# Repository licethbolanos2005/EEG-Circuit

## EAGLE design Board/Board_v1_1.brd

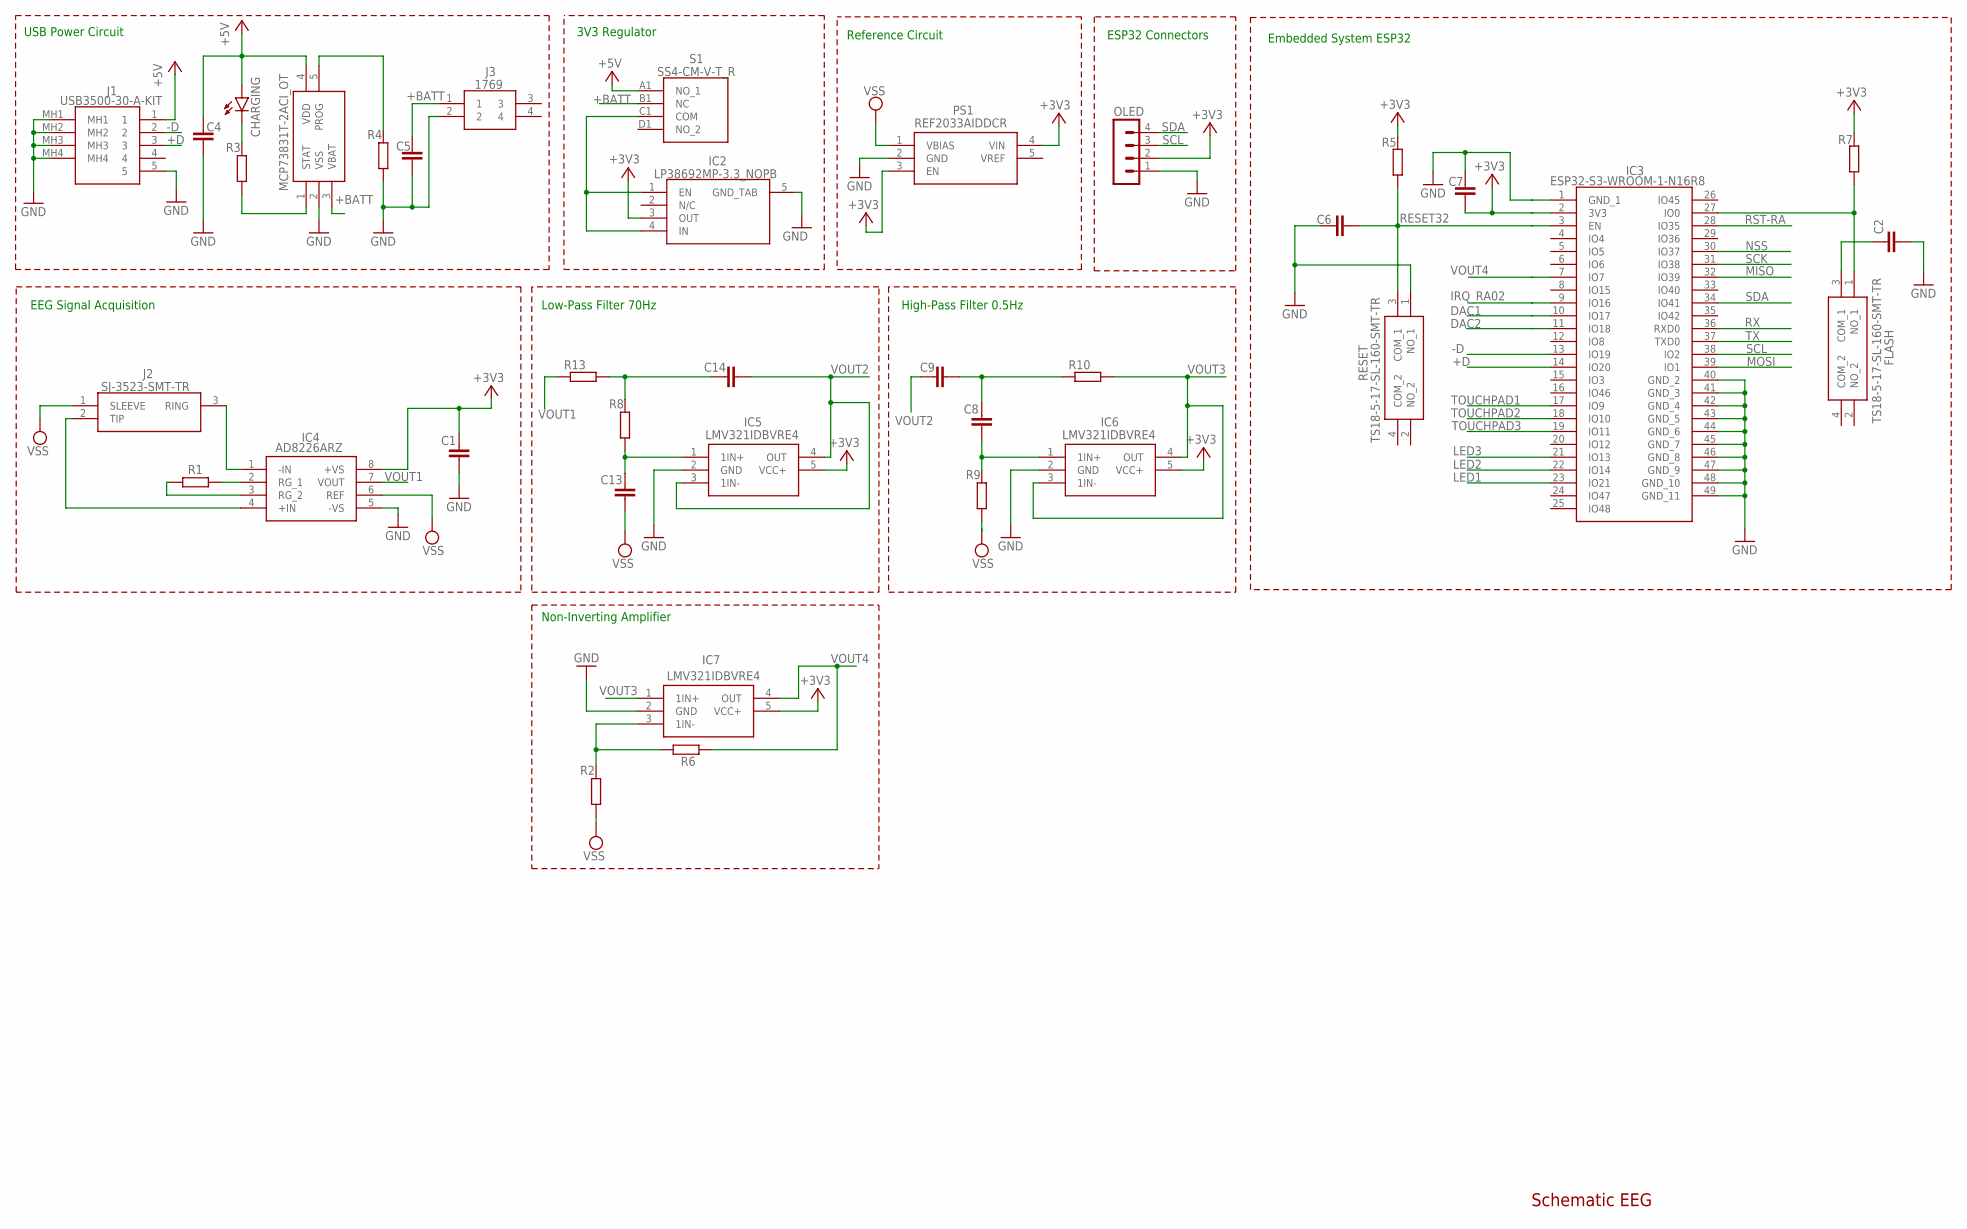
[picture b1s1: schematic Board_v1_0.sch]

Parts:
C1, C2, C4, C5, C6, C7, C8, C9, C13, C14: C-EUC0805; C0805
CHARGING: LEDCHIP-LED0805; CHIP-LED0805
FLASH: TS18-5-17-SL-160-SMT-TR; TS18517SL160SMTTR
IC1: MCP73831T-2ACI_OT; SOT95P270X145-5N
IC2: LP38692MP-3.3_NOPB; SOT150P700X180-5N
IC3: ESP32-S3-WROOM-1-N16R8; ESP32S3WROOM1N16R8
IC4: AD8226ARZ; SOIC127P600X175-8N
IC5, IC6, IC7: LMV321IDBVRE4; SOT95P280X145-5N
J1: USB3500-30-A-KIT; USB350030AKIT
J2: SJ-3523-SMT-TR; SJ3523SMTTR
J3: 1769
OLED: MA04-1
PS1: REF2033AIDDCR; SOT95P280X110-5N
R1, R2, R4, R5, R6, R7, R8, R9, R10, R13: R-EU_R0805; R0805
R3: 220; R0805
RESET: TS18-5-17-SL-160-SMT-TR; TS18517SL160SMTTR
S1: SS4-CM-V-T_R; SS4CMVTR

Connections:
+3V3: C1.1, C7.2, IC2.3 (OUT), IC3.2 (3V3), IC4.8 (+VS), IC5.5 (VCC+), IC6.5 (VCC+), IC7.5 (VCC+), OLED.2, PS1.3 (EN), PS1.4 (VIN), R5.2, R7.2
+BATT: C5.2, IC1.3 (VBAT), J3.1, S1.B1 (NC)
+D: IC3.14 (IO20), J1.3
-D: IC3.13 (IO19), J1.2
DAC1: IC3.10 (IO17)
DAC2: IC3.11 (IO18)
IRQ_RA02: IC3.9 (IO16)
LED1: IC3.23 (IO21)
LED2: IC3.22 (IO14)
LED3: IC3.21 (IO13)
MISO: IC3.32 (IO39)
MOSI: IC3.39 (IO1)
unnamed: IC4.2 (RG_1), R1.2
unnamed: IC4.3 (RG_2), R1.1
unnamed: IC4.1 (-IN), J2.3 (RING)
unnamed: IC4.4 (+IN), J2.2 (TIP)
unnamed: C8.2, IC6.1 (1IN+), R9.2
unnamed: IC1.1 (STAT), R3.1
unnamed: IC1.5 (PROG), R4.2
unnamed 19: CHARGING.C, R3.2; also elsewhere on the board
unnamed: C8.1, C9.2, R10.1
unnamed: C13.1, IC5.1 (1IN+), R8.1
unnamed: IC2.1 (EN), IC2.4 (IN), S1.C1 (COM)
unnamed: IC7.3 (1IN-), R2.2, R6.2
unnamed: C14.1, R8.2, R13.2
NSS: IC3.30 (IO37)
RESET32: C6.2, IC3.3 (EN), R5.1, RESET.3 (COM_1)
RST-RA: IC3.28 (IO35)
RX: IC3.36 (RXD0)
SCK: IC3.31 (IO38)
SCL: IC3.38 (IO2), OLED.3
SDA: IC3.34 (IO41), OLED.4
TOUCHPAD1: IC3.17 (IO9)
TOUCHPAD2: IC3.18 (IO10)
TOUCHPAD3: IC3.19 (IO11)
TX: IC3.37 (TXD0)
VOUT1: IC4.7 (VOUT), R13.1
VOUT2: C9.1, C14.2, IC5.3 (1IN-), IC5.4 (OUT)
VOUT3: IC6.3 (1IN-), IC6.4 (OUT), IC7.1 (1IN+), R10.2
VOUT4: IC3.7 (IO7), IC7.4 (OUT), R6.1
VSS: C13.2, IC4.6 (REF), J2.1 (SLEEVE), PS1.1 (VBIAS), R2.1, R9.1

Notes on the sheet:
Schematic EEG
USB Power Circuit
3V3 Regulator
Reference Circuit
Embedded System ESP32
ESP32 Connectors
Low-Pass Filter 70Hz
High-Pass Filter 0.5Hz
EEG Signal Acquisition
Non-Inverting Amplifier

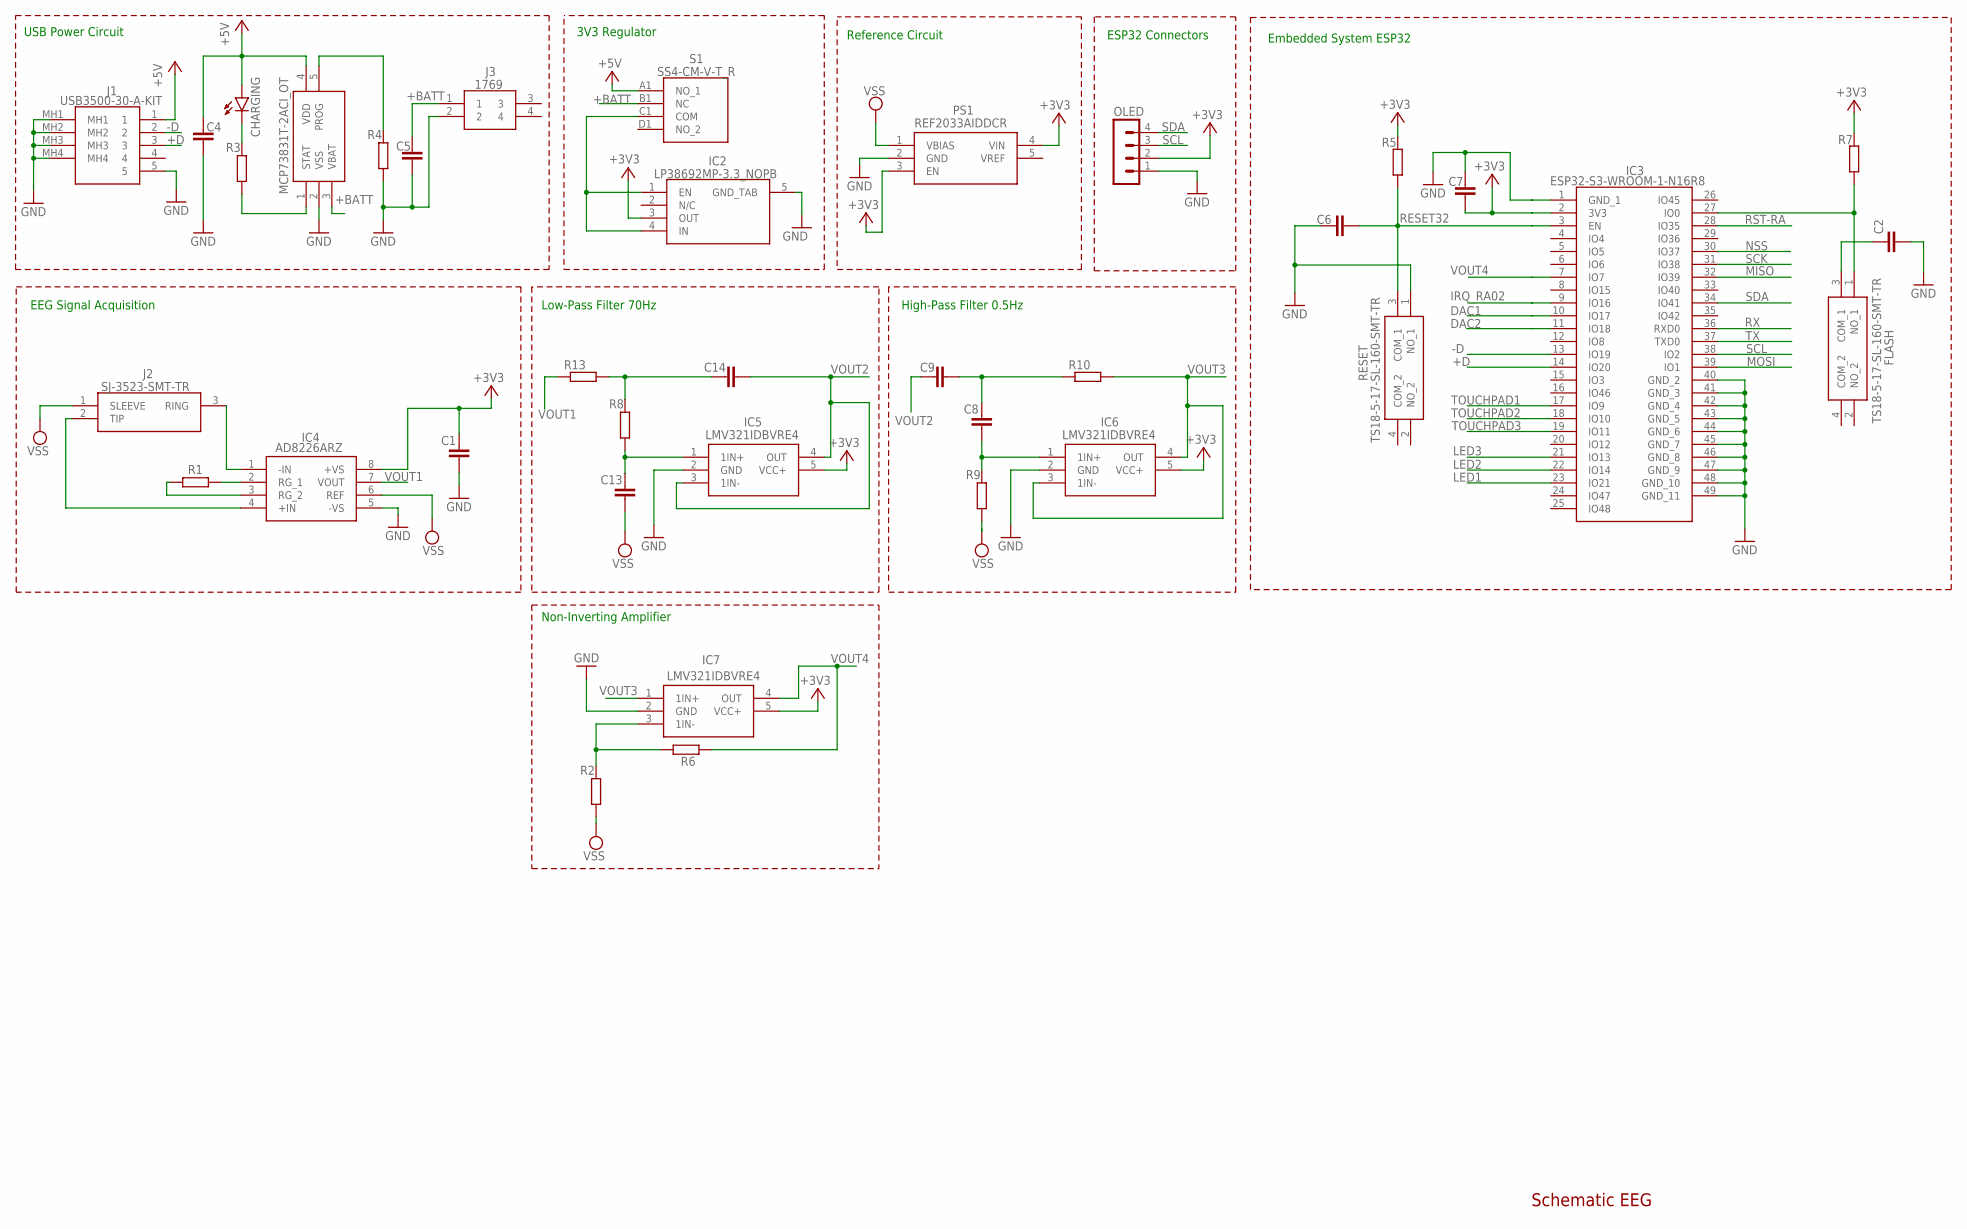
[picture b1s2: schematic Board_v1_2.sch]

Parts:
C1, C2, C4, C5, C6, C7, C8, C9, C13, C14: C-EUC0805; C0805
CHARGING: LEDCHIP-LED0805; CHIP-LED0805
FLASH: TS18-5-17-SL-160-SMT-TR; TS18517SL160SMTTR
IC1: MCP73831T-2ACI_OT; SOT95P270X145-5N
IC2: LP38692MP-3.3_NOPB; SOT150P700X180-5N
IC3: ESP32-S3-WROOM-1-N16R8; ESP32S3WROOM1N16R8
IC4: AD8226ARZ; SOIC127P600X175-8N
IC5, IC6, IC7: LMV321IDBVRE4; SOT95P280X145-5N
J1: USB3500-30-A-KIT; USB350030AKIT
J2: SJ-3523-SMT-TR; SJ3523SMTTR
J3: 1769
OLED: MA04-1
PS1: REF2033AIDDCR; SOT95P280X110-5N
R1, R2, R4, R5, R6, R7, R8, R9, R10, R13: R-EU_R0805; R0805
R3: 220; R0805
RESET: TS18-5-17-SL-160-SMT-TR; TS18517SL160SMTTR
S1: SS4-CM-V-T_R; SS4CMVTR

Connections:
+3V3: C1.1, C7.2, IC2.3 (OUT), IC3.2 (3V3), IC4.8 (+VS), IC5.5 (VCC+), IC6.5 (VCC+), IC7.5 (VCC+), OLED.2, PS1.3 (EN), PS1.4 (VIN), R5.2, R7.2
+BATT: C5.2, IC1.3 (VBAT), J3.1, S1.B1 (NC)
+D: IC3.14 (IO20), J1.3
-D: IC3.13 (IO19), J1.2
DAC1: IC3.10 (IO17)
DAC2: IC3.11 (IO18)
IRQ_RA02: IC3.9 (IO16)
LED1: IC3.23 (IO21)
LED2: IC3.22 (IO14)
LED3: IC3.21 (IO13)
MISO: IC3.32 (IO39)
MOSI: IC3.39 (IO1)
unnamed: IC4.2 (RG_1), R1.2
unnamed: IC4.3 (RG_2), R1.1
unnamed: IC4.1 (-IN), J2.3 (RING)
unnamed: IC4.4 (+IN), J2.2 (TIP)
unnamed: C8.2, IC6.1 (1IN+), R9.2
unnamed: IC1.1 (STAT), R3.1
unnamed: IC1.5 (PROG), R4.2
unnamed 19: CHARGING.C, R3.2; also elsewhere on the board
unnamed: C8.1, C9.2, R10.1
unnamed: C13.1, IC5.1 (1IN+), R8.1
unnamed: IC2.1 (EN), IC2.4 (IN), S1.C1 (COM)
unnamed: IC7.3 (1IN-), R2.2, R6.2
unnamed: C14.1, R8.2, R13.2
NSS: IC3.30 (IO37)
RESET32: C6.2, IC3.3 (EN), R5.1, RESET.3 (COM_1)
RST-RA: IC3.28 (IO35)
RX: IC3.36 (RXD0)
SCK: IC3.31 (IO38)
SCL: IC3.38 (IO2), OLED.3
SDA: IC3.34 (IO41), OLED.4
TOUCHPAD1: IC3.17 (IO9)
TOUCHPAD2: IC3.18 (IO10)
TOUCHPAD3: IC3.19 (IO11)
TX: IC3.37 (TXD0)
VOUT1: IC4.7 (VOUT), R13.1
VOUT2: C9.1, C14.2, IC5.3 (1IN-), IC5.4 (OUT)
VOUT3: IC6.3 (1IN-), IC6.4 (OUT), IC7.1 (1IN+), R10.2
VOUT4: IC3.7 (IO7), IC7.4 (OUT), R6.1
VSS: C13.2, IC4.6 (REF), J2.1 (SLEEVE), PS1.1 (VBIAS), R2.1, R9.1

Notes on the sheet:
Schematic EEG
USB Power Circuit
3V3 Regulator
Reference Circuit
Embedded System ESP32
ESP32 Connectors
Low-Pass Filter 70Hz
High-Pass Filter 0.5Hz
EEG Signal Acquisition
Non-Inverting Amplifier

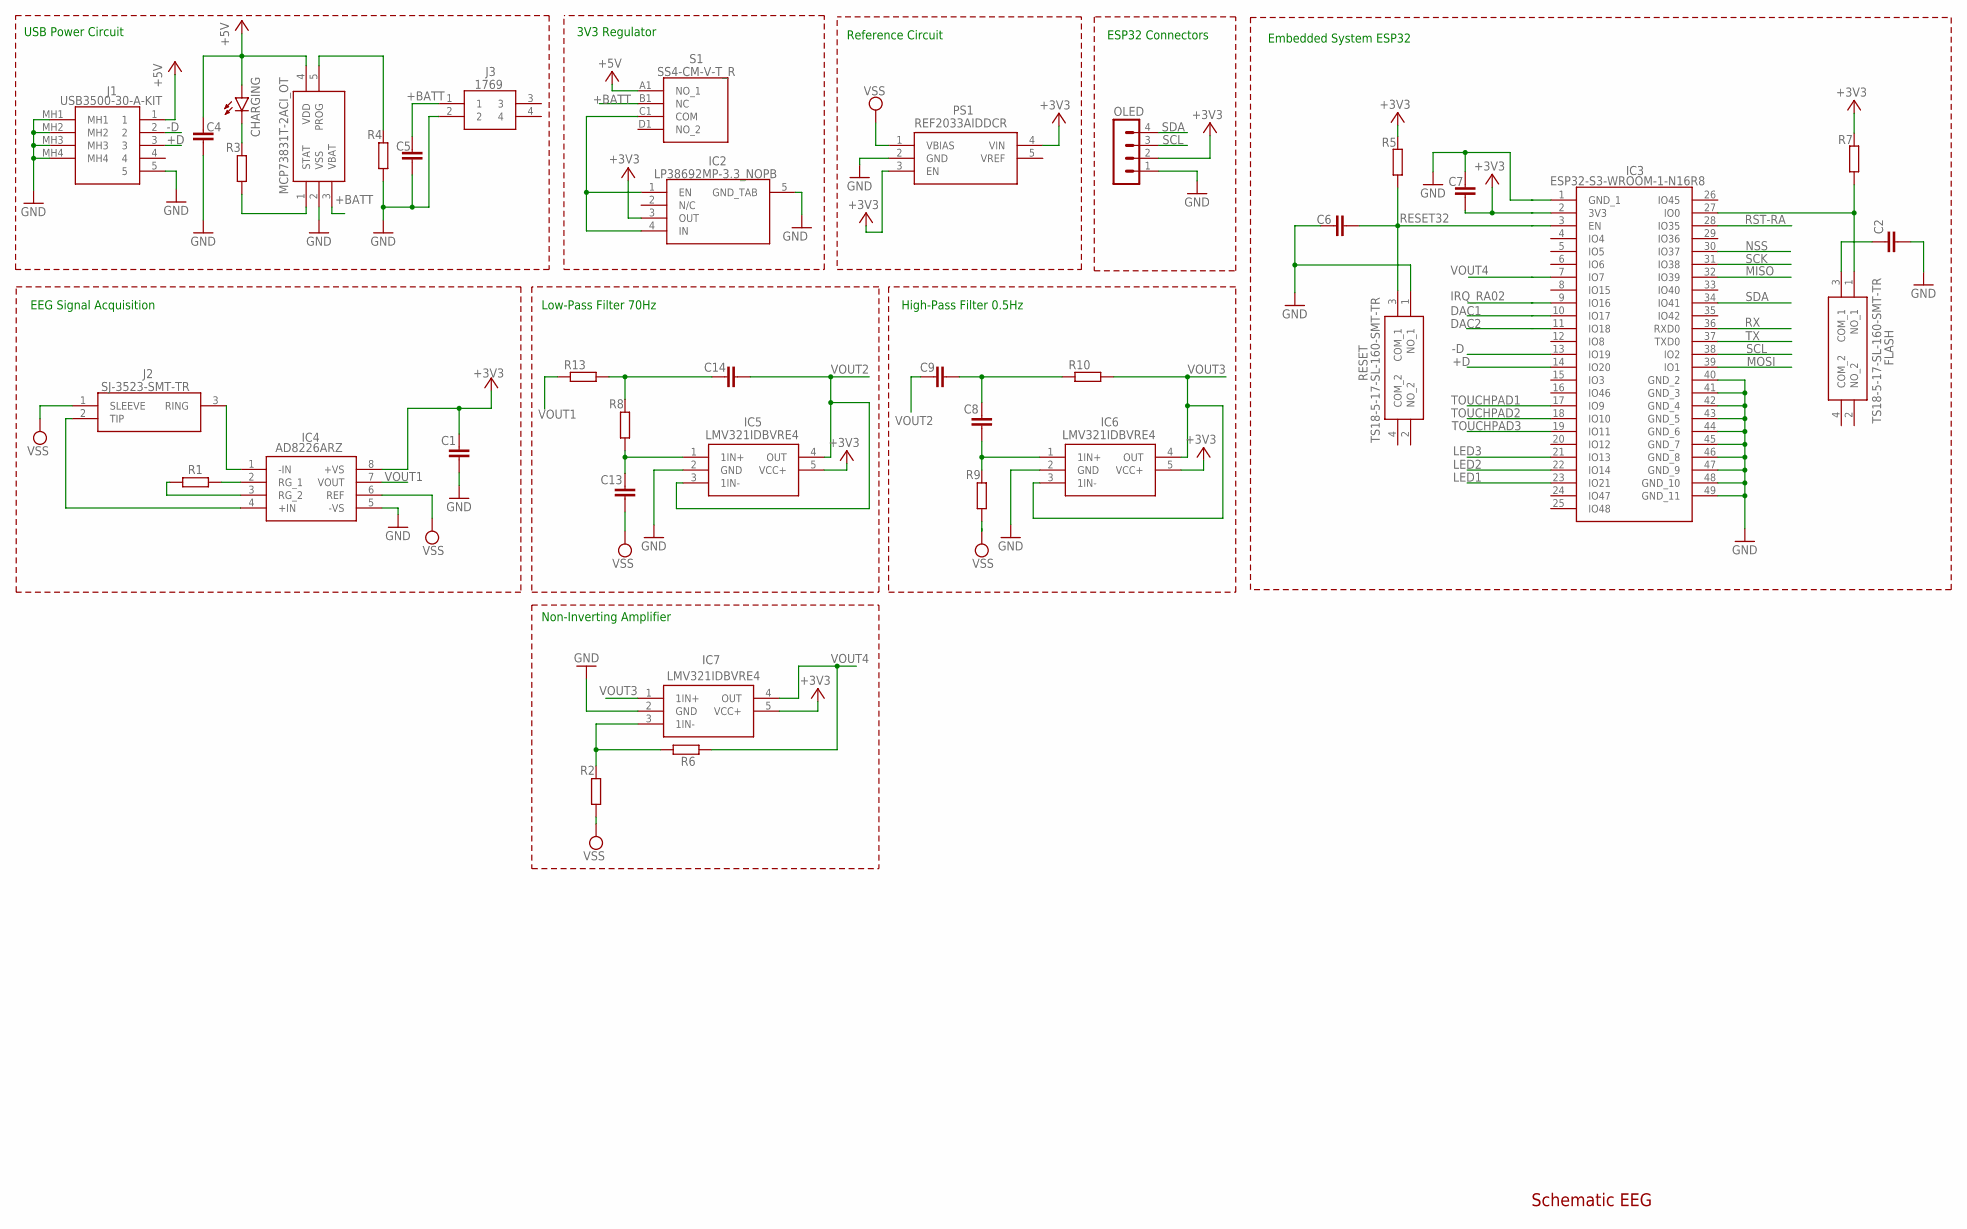
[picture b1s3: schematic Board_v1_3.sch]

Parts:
C1, C2, C4, C5, C6, C7, C8, C9, C13, C14: C-EUC0805; C0805
CHARGING: LEDCHIP-LED0805; CHIP-LED0805
FLASH: TS18-5-17-SL-160-SMT-TR; TS18517SL160SMTTR
IC1: MCP73831T-2ACI_OT; SOT95P270X145-5N
IC2: LP38692MP-3.3_NOPB; SOT150P700X180-5N
IC3: ESP32-S3-WROOM-1-N16R8; ESP32S3WROOM1N16R8
IC4: AD8226ARZ; SOIC127P600X175-8N
IC5, IC6, IC7: LMV321IDBVRE4; SOT95P280X145-5N
J1: USB3500-30-A-KIT; USB350030AKIT
J2: SJ-3523-SMT-TR; SJ3523SMTTR
J3: 1769
OLED: MA04-1
PS1: REF2033AIDDCR; SOT95P280X110-5N
R1, R2, R4, R5, R6, R7, R8, R9, R10, R13: R-EU_R0805; R0805
R3: 220; R0805
RESET: TS18-5-17-SL-160-SMT-TR; TS18517SL160SMTTR
S1: SS4-CM-V-T_R; SS4CMVTR

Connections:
+3V3: C1.1, C7.2, IC2.3 (OUT), IC3.2 (3V3), IC4.8 (+VS), IC5.5 (VCC+), IC6.5 (VCC+), IC7.5 (VCC+), OLED.2, PS1.3 (EN), PS1.4 (VIN), R5.2, R7.2
+BATT: C5.2, IC1.3 (VBAT), J3.1, S1.B1 (NC)
+D: IC3.14 (IO20), J1.3
-D: IC3.13 (IO19), J1.2
DAC1: IC3.10 (IO17)
DAC2: IC3.11 (IO18)
IRQ_RA02: IC3.9 (IO16)
LED1: IC3.23 (IO21)
LED2: IC3.22 (IO14)
LED3: IC3.21 (IO13)
MISO: IC3.32 (IO39)
MOSI: IC3.39 (IO1)
unnamed: IC4.2 (RG_1), R1.2
unnamed: IC4.3 (RG_2), R1.1
unnamed: IC4.1 (-IN), J2.3 (RING)
unnamed: IC4.4 (+IN), J2.2 (TIP)
unnamed: C8.2, IC6.1 (1IN+), R9.2
unnamed: IC1.1 (STAT), R3.1
unnamed: IC1.5 (PROG), R4.2
unnamed 19: CHARGING.C, R3.2; also elsewhere on the board
unnamed: C8.1, C9.2, R10.1
unnamed: C13.1, IC5.1 (1IN+), R8.1
unnamed: IC2.1 (EN), IC2.4 (IN), S1.C1 (COM)
unnamed: IC7.3 (1IN-), R2.2, R6.2
unnamed: C14.1, R8.2, R13.2
NSS: IC3.30 (IO37)
RESET32: C6.2, IC3.3 (EN), R5.1, RESET.3 (COM_1)
RST-RA: IC3.28 (IO35)
RX: IC3.36 (RXD0)
SCK: IC3.31 (IO38)
SCL: IC3.38 (IO2), OLED.3
SDA: IC3.34 (IO41), OLED.4
TOUCHPAD1: IC3.17 (IO9)
TOUCHPAD2: IC3.18 (IO10)
TOUCHPAD3: IC3.19 (IO11)
TX: IC3.37 (TXD0)
VOUT1: IC4.7 (VOUT), R13.1
VOUT2: C9.1, C14.2, IC5.3 (1IN-), IC5.4 (OUT)
VOUT3: IC6.3 (1IN-), IC6.4 (OUT), IC7.1 (1IN+), R10.2
VOUT4: IC3.7 (IO7), IC7.4 (OUT), R6.1
VSS: C13.2, IC4.6 (REF), J2.1 (SLEEVE), PS1.1 (VBIAS), R2.1, R9.1

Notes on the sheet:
Schematic EEG
USB Power Circuit
3V3 Regulator
Reference Circuit
Embedded System ESP32
ESP32 Connectors
Low-Pass Filter 70Hz
High-Pass Filter 0.5Hz
EEG Signal Acquisition
Non-Inverting Amplifier

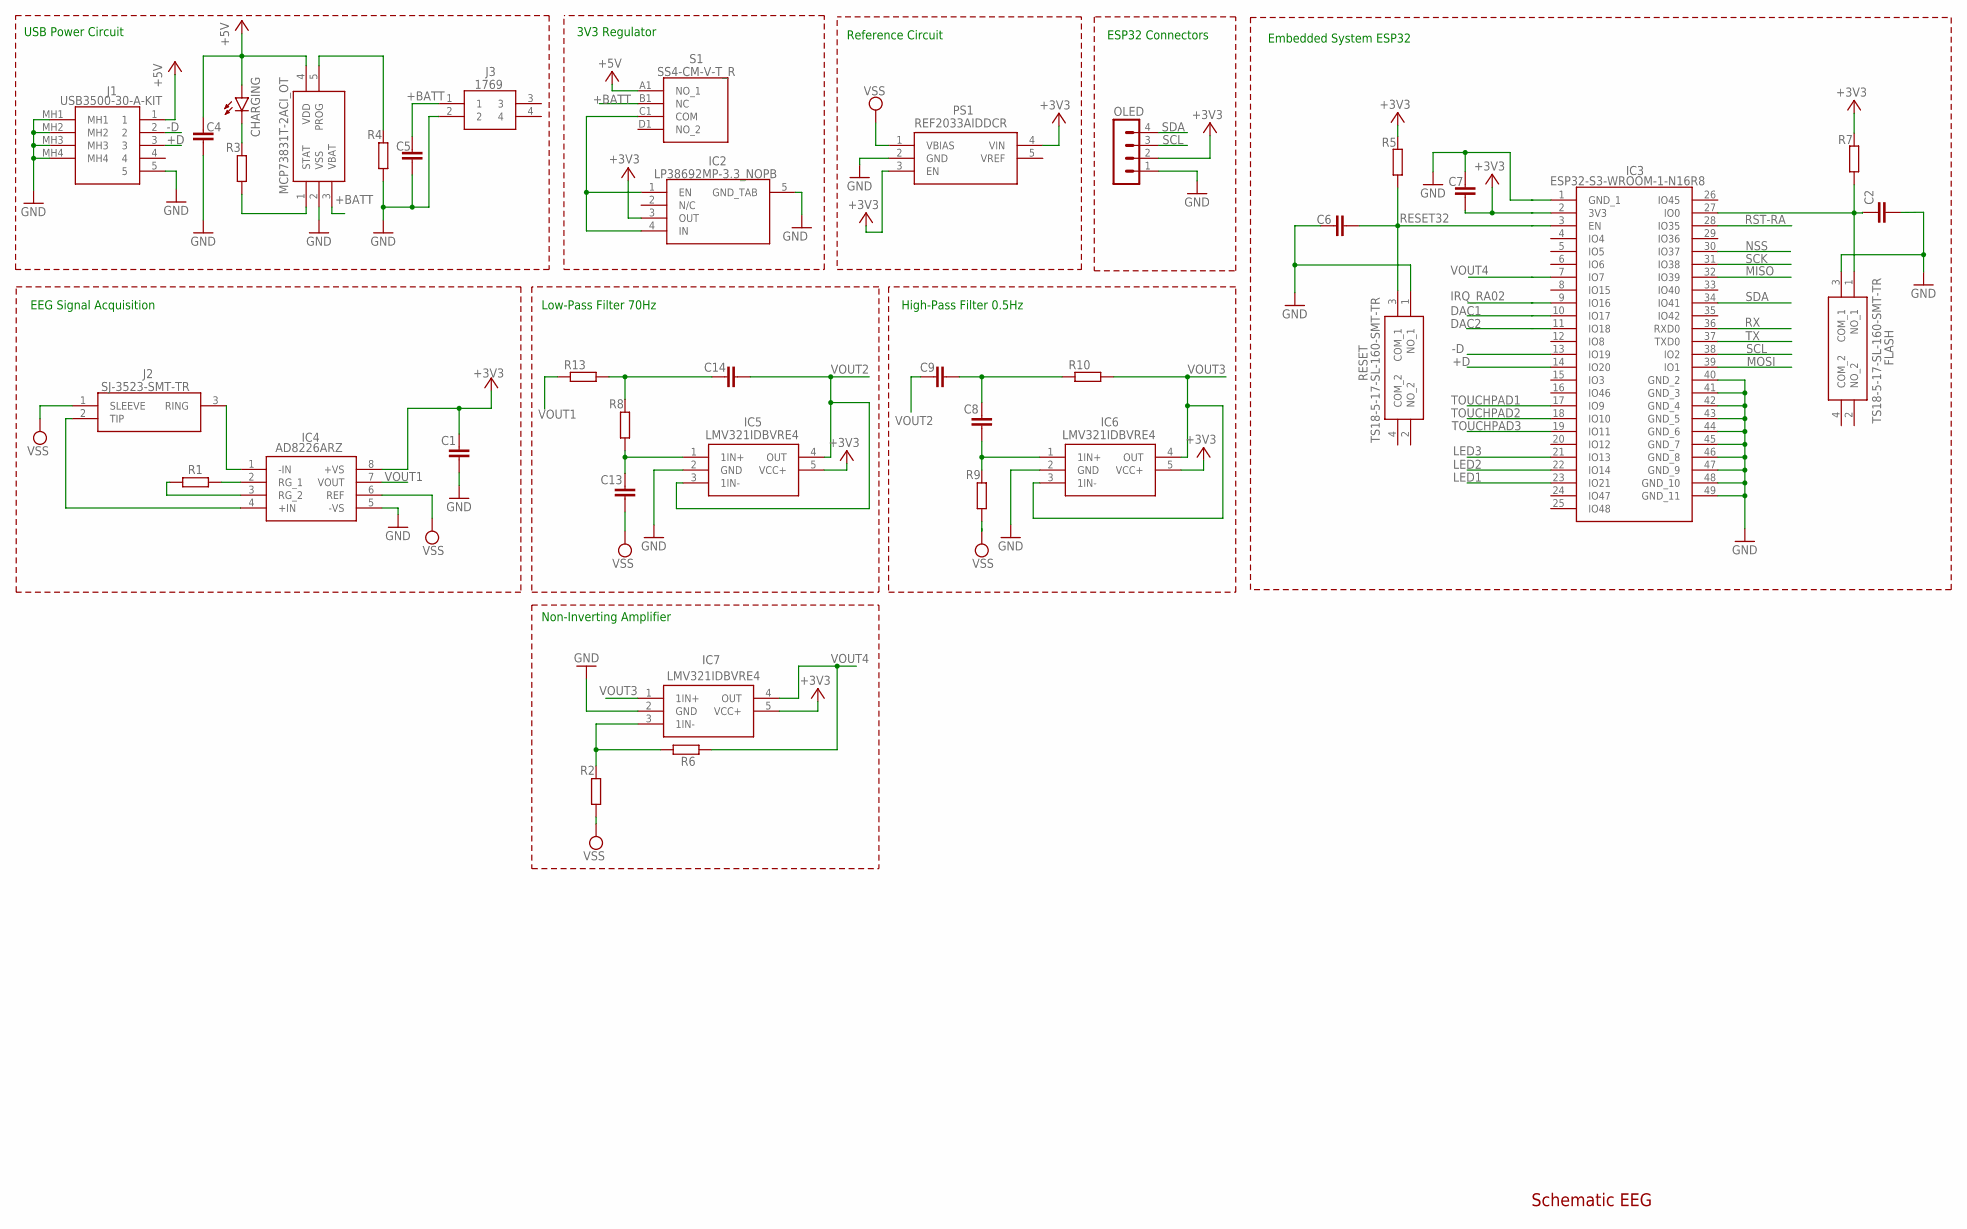
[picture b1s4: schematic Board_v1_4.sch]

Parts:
C1, C2, C4, C5, C6, C7, C8, C9, C13, C14: C-EUC0805; C0805
CHARGING: LEDCHIP-LED0805; CHIP-LED0805
FLASH: TS18-5-17-SL-160-SMT-TR; TS18517SL160SMTTR
IC1: MCP73831T-2ACI_OT; SOT95P270X145-5N
IC2: LP38692MP-3.3_NOPB; SOT150P700X180-5N
IC3: ESP32-S3-WROOM-1-N16R8; ESP32S3WROOM1N16R8
IC4: AD8226ARZ; SOIC127P600X175-8N
IC5, IC6, IC7: LMV321IDBVRE4; SOT95P280X145-5N
J1: USB3500-30-A-KIT; USB350030AKIT
J2: SJ-3523-SMT-TR; SJ3523SMTTR
J3: 1769
OLED: MA04-1
PS1: REF2033AIDDCR; SOT95P280X110-5N
R1, R2, R4, R5, R6, R7, R8, R9, R10, R13: R-EU_R0805; R0805
R3: 220; R0805
RESET: TS18-5-17-SL-160-SMT-TR; TS18517SL160SMTTR
S1: SS4-CM-V-T_R; SS4CMVTR

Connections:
+3V3: C1.1, C7.2, IC2.3 (OUT), IC3.2 (3V3), IC4.8 (+VS), IC5.5 (VCC+), IC6.5 (VCC+), IC7.5 (VCC+), OLED.2, PS1.3 (EN), PS1.4 (VIN), R5.2, R7.2
+BATT: C5.2, IC1.3 (VBAT), J3.1, S1.B1 (NC)
+D: IC3.14 (IO20), J1.3
-D: IC3.13 (IO19), J1.2
DAC1: IC3.10 (IO17)
DAC2: IC3.11 (IO18)
IRQ_RA02: IC3.9 (IO16)
LED1: IC3.23 (IO21)
LED2: IC3.22 (IO14)
LED3: IC3.21 (IO13)
MISO: IC3.32 (IO39)
MOSI: IC3.39 (IO1)
unnamed: IC4.2 (RG_1), R1.2
unnamed: IC4.3 (RG_2), R1.1
unnamed: IC4.1 (-IN), J2.3 (RING)
unnamed: IC4.4 (+IN), J2.2 (TIP)
unnamed: C8.2, IC6.1 (1IN+), R9.2
unnamed: IC1.1 (STAT), R3.1
unnamed: IC1.5 (PROG), R4.2
unnamed 19: CHARGING.C, R3.2; also elsewhere on the board
unnamed: C8.1, C9.2, R10.1
unnamed: C13.1, IC5.1 (1IN+), R8.1
unnamed: IC2.1 (EN), IC2.4 (IN), S1.C1 (COM)
unnamed: IC7.3 (1IN-), R2.2, R6.2
unnamed: C14.1, R8.2, R13.2
NSS: IC3.30 (IO37)
RESET32: C6.2, IC3.3 (EN), R5.1, RESET.3 (COM_1)
RST-RA: IC3.28 (IO35)
RX: IC3.36 (RXD0)
SCK: IC3.31 (IO38)
SCL: IC3.38 (IO2), OLED.3
SDA: IC3.34 (IO41), OLED.4
TOUCHPAD1: IC3.17 (IO9)
TOUCHPAD2: IC3.18 (IO10)
TOUCHPAD3: IC3.19 (IO11)
TX: IC3.37 (TXD0)
VOUT1: IC4.7 (VOUT), R13.1
VOUT2: C9.1, C14.2, IC5.3 (1IN-), IC5.4 (OUT)
VOUT3: IC6.3 (1IN-), IC6.4 (OUT), IC7.1 (1IN+), R10.2
VOUT4: IC3.7 (IO7), IC7.4 (OUT), R6.1
VSS: C13.2, IC4.6 (REF), J2.1 (SLEEVE), PS1.1 (VBIAS), R2.1, R9.1

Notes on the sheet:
Schematic EEG
USB Power Circuit
3V3 Regulator
Reference Circuit
Embedded System ESP32
ESP32 Connectors
Low-Pass Filter 70Hz
High-Pass Filter 0.5Hz
EEG Signal Acquisition
Non-Inverting Amplifier

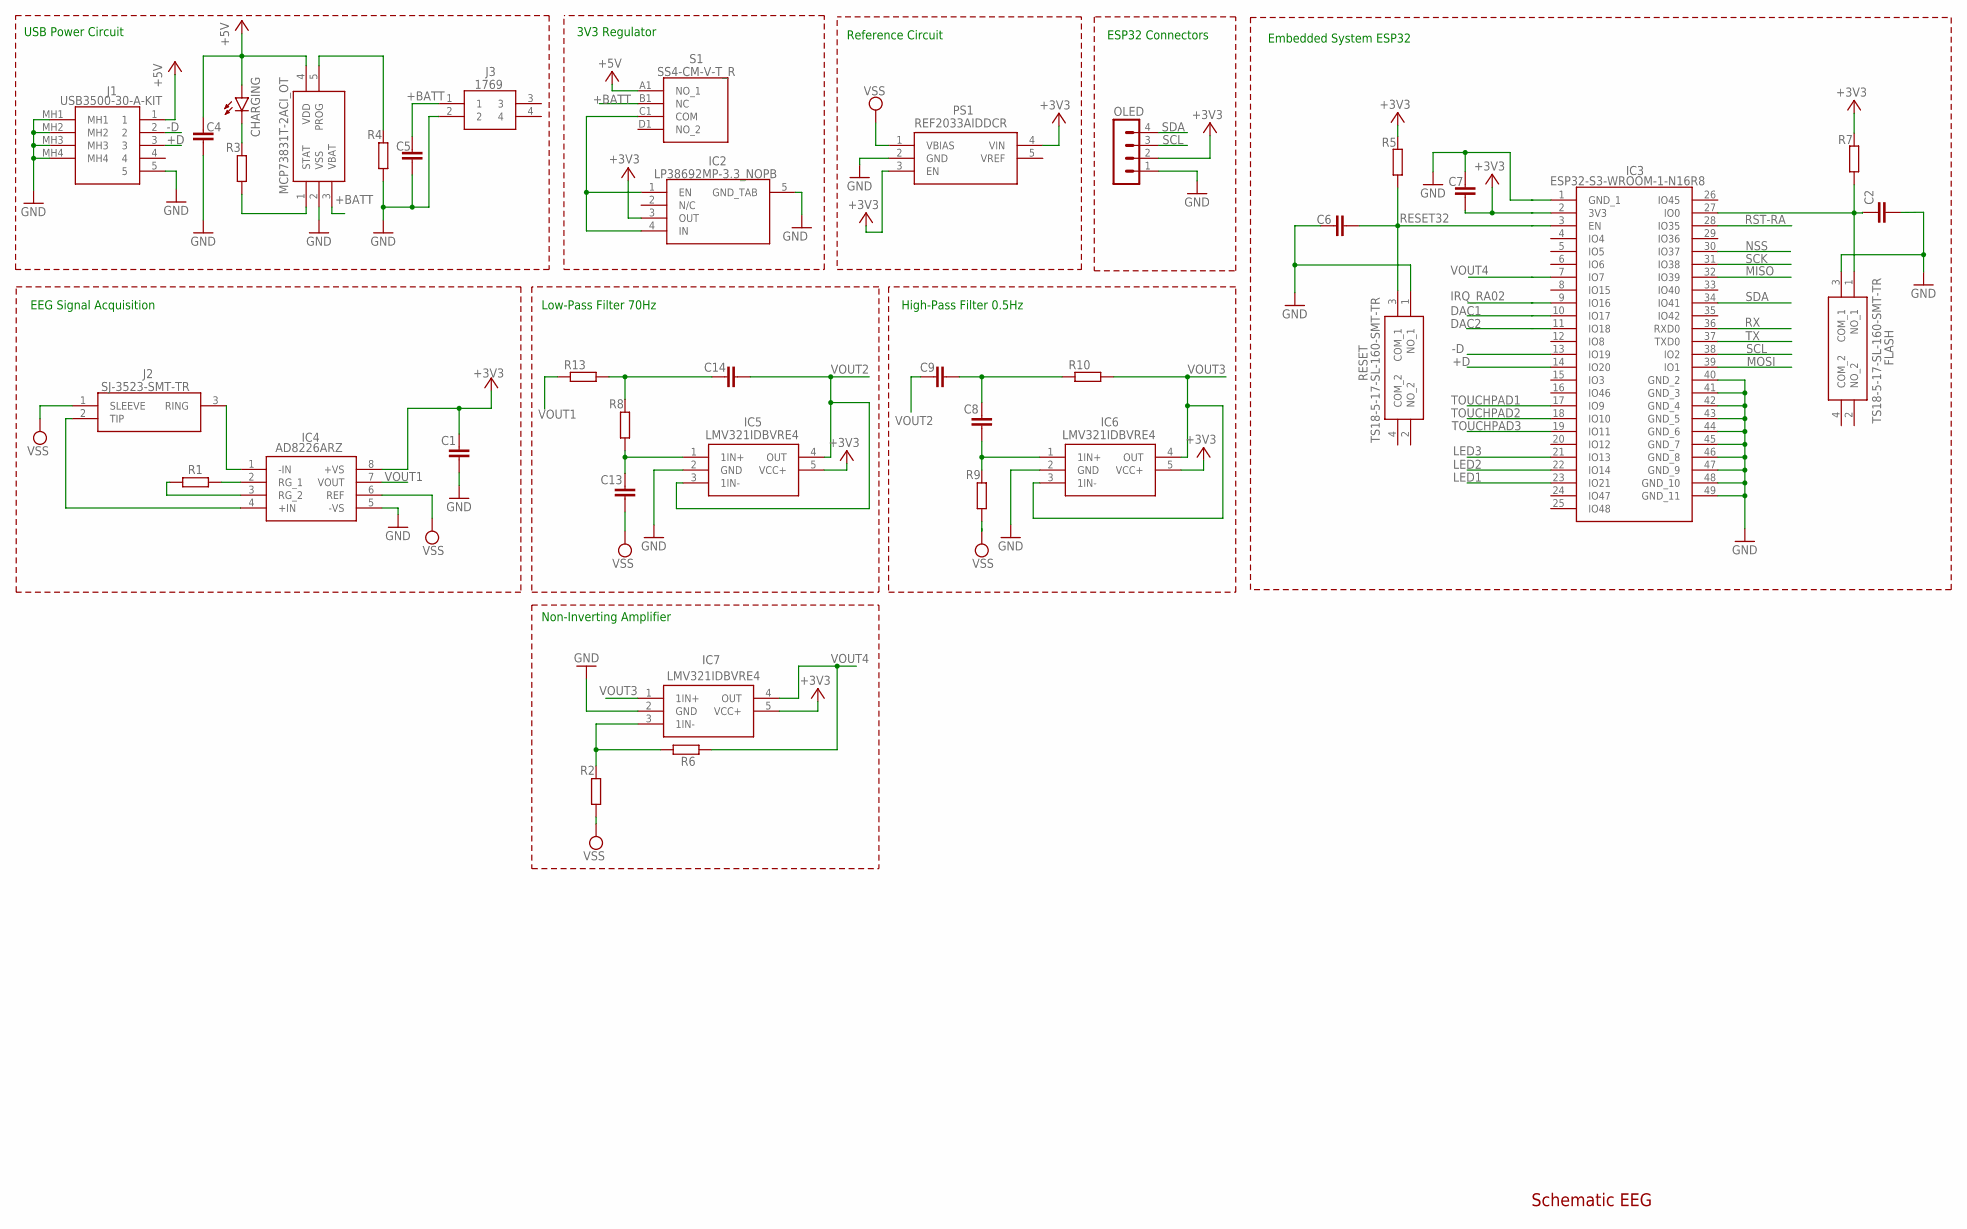
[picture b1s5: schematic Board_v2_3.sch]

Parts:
C1, C2, C4, C5, C6, C7, C8, C9, C13, C14: C-EUC0805; C0805
CHARGING: LEDCHIP-LED0805; CHIP-LED0805
FLASH: TS18-5-17-SL-160-SMT-TR; TS18517SL160SMTTR
IC1: MCP73831T-2ACI_OT; SOT95P270X145-5N
IC2: LP38692MP-3.3_NOPB; SOT150P700X180-5N
IC3: ESP32-S3-WROOM-1-N16R8; ESP32S3WROOM1N16R8
IC4: AD8226ARZ; SOIC127P600X175-8N
IC5, IC6, IC7: LMV321IDBVRE4; SOT95P280X145-5N
J1: USB3500-30-A-KIT; USB350030AKIT
J2: SJ-3523-SMT-TR; SJ3523SMTTR
J3: 1769
OLED: MA04-1
PS1: REF2033AIDDCR; SOT95P280X110-5N
R1, R2, R4, R5, R6, R7, R8, R9, R10, R13: R-EU_R0805; R0805
R3: 220; R0805
RESET: TS18-5-17-SL-160-SMT-TR; TS18517SL160SMTTR
S1: SS4-CM-V-T_R; SS4CMVTR

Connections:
+3V3: C1.1, C7.2, IC2.3 (OUT), IC3.2 (3V3), IC4.8 (+VS), IC5.5 (VCC+), IC6.5 (VCC+), IC7.5 (VCC+), OLED.2, PS1.3 (EN), PS1.4 (VIN), R5.2, R7.2
+BATT: C5.2, IC1.3 (VBAT), J3.1, S1.B1 (NC)
+D: IC3.14 (IO20), J1.3
-D: IC3.13 (IO19), J1.2
DAC1: IC3.10 (IO17)
DAC2: IC3.11 (IO18)
IRQ_RA02: IC3.9 (IO16)
LED1: IC3.23 (IO21)
LED2: IC3.22 (IO14)
LED3: IC3.21 (IO13)
MISO: IC3.32 (IO39)
MOSI: IC3.39 (IO1)
unnamed: IC4.2 (RG_1), R1.2
unnamed: IC4.3 (RG_2), R1.1
unnamed: IC4.1 (-IN), J2.3 (RING)
unnamed: IC4.4 (+IN), J2.2 (TIP)
unnamed: C8.2, IC6.1 (1IN+), R9.2
unnamed: IC1.1 (STAT), R3.1
unnamed: IC1.5 (PROG), R4.2
unnamed 19: CHARGING.C, R3.2; also elsewhere on the board
unnamed: C8.1, C9.2, R10.1
unnamed: C13.1, IC5.1 (1IN+), R8.1
unnamed: IC2.1 (EN), IC2.4 (IN), S1.C1 (COM)
unnamed: IC7.3 (1IN-), R2.2, R6.2
unnamed: C14.1, R8.2, R13.2
NSS: IC3.30 (IO37)
RESET32: C6.2, IC3.3 (EN), R5.1, RESET.3 (COM_1)
RST-RA: IC3.28 (IO35)
RX: IC3.36 (RXD0)
SCK: IC3.31 (IO38)
SCL: IC3.38 (IO2), OLED.3
SDA: IC3.34 (IO41), OLED.4
TOUCHPAD1: IC3.17 (IO9)
TOUCHPAD2: IC3.18 (IO10)
TOUCHPAD3: IC3.19 (IO11)
TX: IC3.37 (TXD0)
VOUT1: IC4.7 (VOUT), R13.1
VOUT2: C9.1, C14.2, IC5.3 (1IN-), IC5.4 (OUT)
VOUT3: IC6.3 (1IN-), IC6.4 (OUT), IC7.1 (1IN+), R10.2
VOUT4: IC3.7 (IO7), IC7.4 (OUT), R6.1
VSS: C13.2, IC4.6 (REF), J2.1 (SLEEVE), PS1.1 (VBIAS), R2.1, R9.1

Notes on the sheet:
Schematic EEG
USB Power Circuit
3V3 Regulator
Reference Circuit
Embedded System ESP32
ESP32 Connectors
Low-Pass Filter 70Hz
High-Pass Filter 0.5Hz
EEG Signal Acquisition
Non-Inverting Amplifier

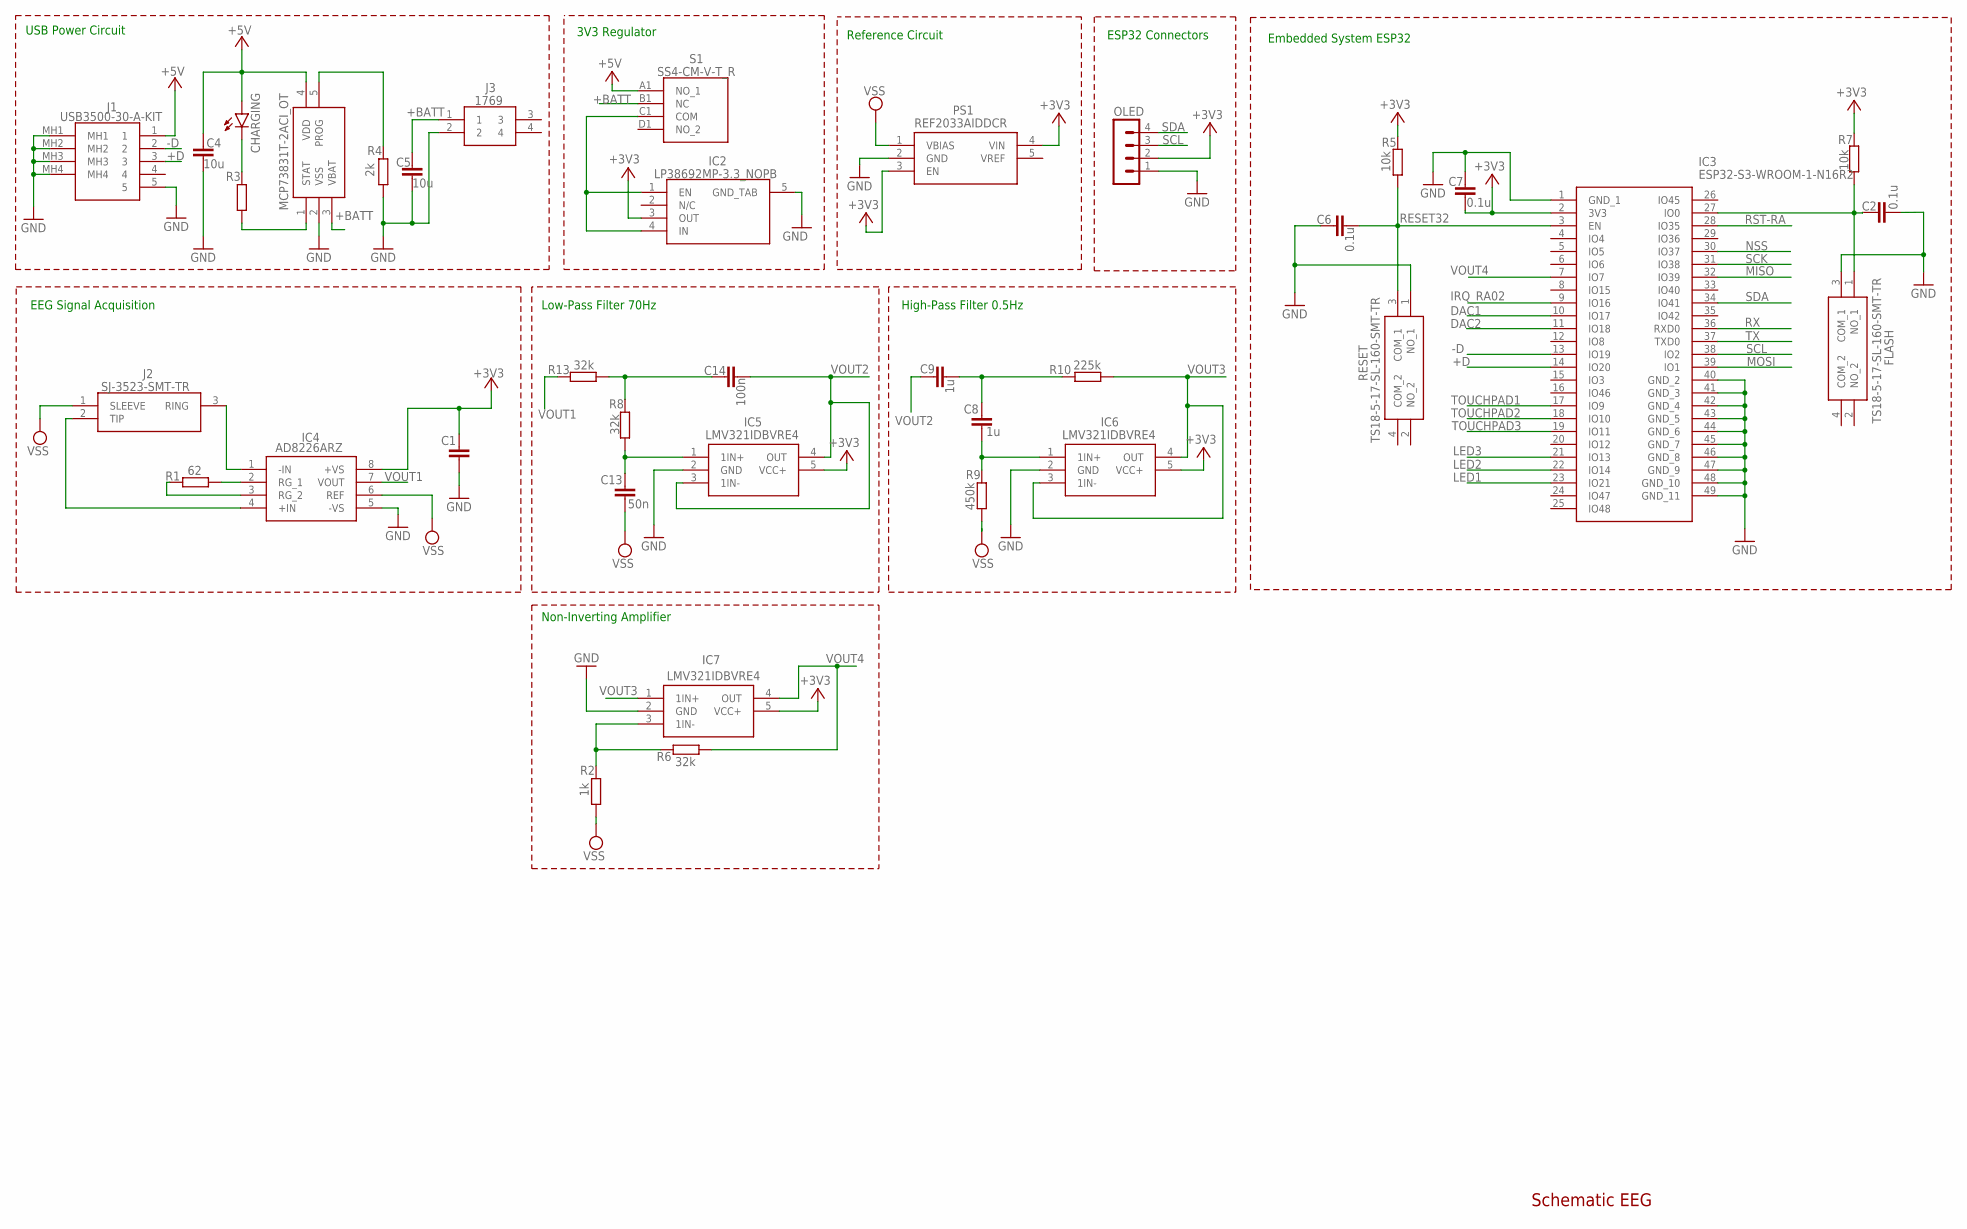
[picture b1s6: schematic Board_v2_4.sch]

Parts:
C1: C-EUC0805; C0805
C2, C6, C7: 0.1u; C0805
C4, C5: 10u; C0805
C8, C9: 1u; C0805
C13: 50n; C0805
C14: 100n; C0805
CHARGING: LEDCHIP-LED0805; CHIP-LED0805
FLASH: TS18-5-17-SL-160-SMT-TR; TS18517SL160SMTTR
IC1: MCP73831T-2ACI_OT; SOT95P270X145-5N
IC2: LP38692MP-3.3_NOPB; SOT150P700X180-5N
IC3: ESP32-S3-WROOM-1-N16R2; ESP32S3WROOM1N16R2
IC4: AD8226ARZ; SOIC127P600X175-8N
IC5, IC6, IC7: LMV321IDBVRE4; SOT95P280X145-5N
J1: USB3500-30-A-KIT; USB350030AKIT
J2: SJ-3523-SMT-TR; SJ3523SMTTR
J3: 1769
OLED: MA04-1
PS1: REF2033AIDDCR; SOT95P280X110-5N
R1: 62; R0805
R2: 1k; R0805
R3: 220; R0805
R4: 2k; R0805
R5, R7: 10k; R0805
R6, R8, R13: 32k; R0805
R9: 450k; R0805
R10: 225k; R0805
RESET: TS18-5-17-SL-160-SMT-TR; TS18517SL160SMTTR
S1: SS4-CM-V-T_R; SS4CMVTR

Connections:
+3V3: C1.1, C7.2, IC2.3 (OUT), IC3.2 (3V3), IC4.8 (+VS), IC5.5 (VCC+), IC6.5 (VCC+), IC7.5 (VCC+), OLED.2, PS1.3 (EN), PS1.4 (VIN), R5.2, R7.2
+BATT: C5.2, IC1.3 (VBAT), J3.1, S1.B1 (NC)
+D: IC3.14 (IO20), J1.3
-D: IC3.13 (IO19), J1.2
DAC1: IC3.10 (IO17)
DAC2: IC3.11 (IO18)
IRQ_RA02: IC3.9 (IO16)
LED1: IC3.23 (IO21)
LED2: IC3.22 (IO14)
LED3: IC3.21 (IO13)
MISO: IC3.32 (IO39)
MOSI: IC3.39 (IO1)
unnamed: IC4.2 (RG_1), R1.2
unnamed: IC4.3 (RG_2), R1.1
unnamed: IC4.1 (-IN), J2.3 (RING)
unnamed: IC4.4 (+IN), J2.2 (TIP)
unnamed: C8.2, IC6.1 (1IN+), R9.2
unnamed: IC1.1 (STAT), R3.1
unnamed: IC1.5 (PROG), R4.2
unnamed 19: CHARGING.C, R3.2; also elsewhere on the board
unnamed: C8.1, C9.2, R10.1
unnamed: C13.1, IC5.1 (1IN+), R8.1
unnamed: IC2.1 (EN), IC2.4 (IN), S1.C1 (COM)
unnamed: IC7.3 (1IN-), R2.2, R6.2
unnamed: C14.1, R8.2, R13.2
NSS: IC3.30 (IO37)
RESET32: C6.2, IC3.3 (EN), R5.1, RESET.3 (COM_1)
RST-RA: IC3.28 (IO35)
RX: IC3.36 (RXD0)
SCK: IC3.31 (IO38)
SCL: IC3.38 (IO2), OLED.3
SDA: IC3.34 (IO41), OLED.4
TOUCHPAD1: IC3.17 (IO9)
TOUCHPAD2: IC3.18 (IO10)
TOUCHPAD3: IC3.19 (IO11)
TX: IC3.37 (TXD0)
VOUT1: IC4.7 (VOUT), R13.1
VOUT2: C9.1, C14.2, IC5.3 (1IN-), IC5.4 (OUT)
VOUT3: IC6.3 (1IN-), IC6.4 (OUT), IC7.1 (1IN+), R10.2
VOUT4: IC3.7 (IO7), IC7.4 (OUT), R6.1
VSS: C13.2, IC4.6 (REF), J2.1 (SLEEVE), PS1.1 (VBIAS), R2.1, R9.1

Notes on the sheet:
Schematic EEG
USB Power Circuit
3V3 Regulator
Reference Circuit
Embedded System ESP32
ESP32 Connectors
Low-Pass Filter 70Hz
High-Pass Filter 0.5Hz
EEG Signal Acquisition
Non-Inverting Amplifier
